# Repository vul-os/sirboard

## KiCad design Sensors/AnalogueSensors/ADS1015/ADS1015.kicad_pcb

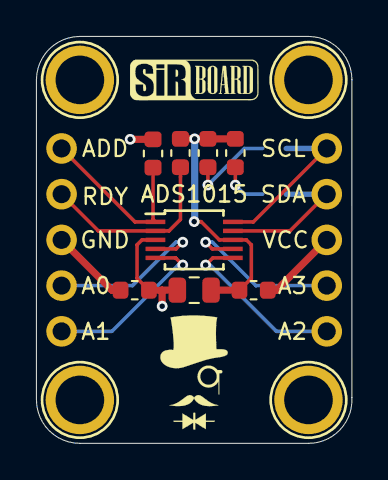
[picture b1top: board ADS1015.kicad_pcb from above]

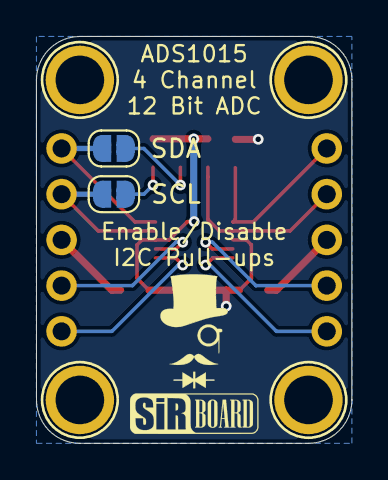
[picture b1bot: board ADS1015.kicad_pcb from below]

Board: 2 copper layers, 17.5 x 22.6 mm, 16 parts (4 on the bottom side), 14 nets.

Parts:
ADS1015: ADS1015IDGS; TSSOP-10_3x3mm_P0.5mm
C1: 1uF; C_0805_2012Metric
FB1, FB2: Ferrite_Bead; L_0603_1608Metric
H1, H2, H3, H4: MountingHole; MountingHole_M2.5_SirBoard
J1, J2: Conn_01x05; PinHeader_1x05_P2.54mm_Vertical
R1, R2, R3, R4: 10K; R_0603_1608Metric
SCL: SolderJumper_2_Open; SolderJumper-2_P1.3mm_Open_RoundedPad1.0x1.5mm
SDA: SolderJumper_2_Open; SolderJumper-2_P1.3mm_Open_RoundedPad1.0x1.5mm

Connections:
ADD: ADS1015.1, J1.1, R4.1
AIN0: ADS1015.4, J1.4
AIN1: ADS1015.5, J1.5
AIN2: ADS1015.6, J2.5
AIN3: ADS1015.7, J2.4
ALERT: ADS1015.2, J1.2, R3.1
GND: FB1.1, J1.3
GND_B: ADS1015.3, C1.2, FB1.2, R4.2
unnamed: R1.1, SCL.2
unnamed: R2.1, SDA.2
SCL: ADS1015.10, J2.1, SDA.1
SDA: ADS1015.9, J2.2, SCL.1
VCC: FB2.1, J2.3
VCC_B: ADS1015.8, C1.1, FB2.2, R1.2, R2.2, R3.2

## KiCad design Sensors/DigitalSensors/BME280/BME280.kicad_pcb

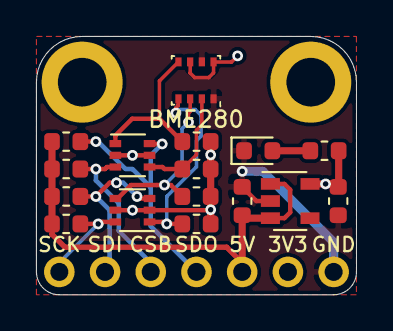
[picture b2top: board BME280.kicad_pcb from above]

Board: 2 copper layers, 17.8 x 14.4 mm, 19 parts (1 on the bottom side), 12 nets.

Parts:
BME280: BME280; Bosch_LGA-8_2.5x2.5mm_P0.65mm_ClockwisePinNumbering
C1, C2: 1uF; C_0603_1608Metric
D1: LED; LED_0603_1608Metric
H3, H4: MountingHole; MountingHole_2.7mm_M2.5_ISO14580_Pad
J1: Conn_01x07; PinHeader_1x07_P2.54mm_Vertical
Q1, Q2: BSS138DW; SOT-363_SC-70-6
R1, R2, R3, R4, R5, R7, R8, R9: 10K; R_0603_1608Metric
R6: 1K; R_0603_1608Metric
U1: AP2127K-3.3; SOT-23-5

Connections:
3V3: BME280.6, BME280.8, C2.1, J1.6, Q1.2, Q1.5, Q2.2, Q2.5, R1.2, R3.2, R5.2, R6.1, R8.2, U1.5
5V: C1.1, J1.5, R2.1, R4.1, R7.1, R9.1, U1.1, U1.3
CSB_3V3: BME280.2, Q2.4, R8.1
CSB_5V: J1.3, Q2.3, R9.2
GND: BME280.1, BME280.7, C1.2, C2.2, D1.1, J1.7, U1.2
unnamed: D1.2, R6.2
SCK_3V3: BME280.4, Q1.1, R1.1
SCK_5V: J1.1, Q1.6, R2.2
SDI_3V3: BME280.3, Q1.4, R3.1
SDI_5V: J1.2, Q1.3, R4.2
SDO_3V3: BME280.5, Q2.1, R5.1
SDO_5V: J1.4, Q2.6, R7.2

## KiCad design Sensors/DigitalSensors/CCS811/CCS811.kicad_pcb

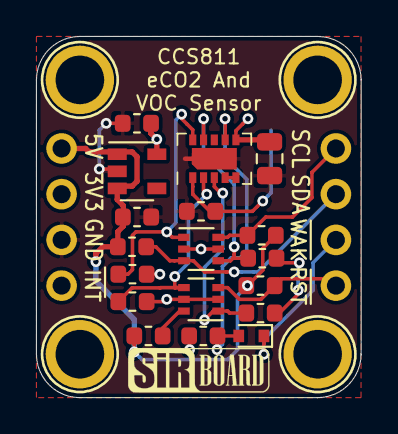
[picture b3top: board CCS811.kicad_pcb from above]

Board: 2 copper layers, 18.0 x 20.1 mm, 25 parts (1 on the bottom side), 15 nets.

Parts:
C1, C3: 1uF; C_0603_1608Metric
C5: 4.7uF; C_0805_2012Metric
D1: 1N4148; D_SOD-523
H1, H2, H3, H4: MountingHole; MountingHole_M2.5_SirBoard
J1, J2: Conn_01x04; PinHeader_1x04_P2.54mm_Vertical
JP1: SolderJumper_2_Open; SolderJumper-2_P1.3mm_Open_RoundedPad1.0x1.5mm
Q1, Q2: BSS138DW; SOT-363_SC-70-6
R1, R2, R3, R4, R5, R6, R7, R9: 4K7; R_0603_1608Metric
R8: 100K; R_0603_1608Metric
R11: 10K; R_0603_1608Metric
U1: AP2127K-3.3; SOT-23-5
U2: CCS811; AMS_LGA-10-1EP_2.7x4mm_P0.6mm

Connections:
3V3: C3.1, C5.1, J1.2, JP1.1, Q1.2, Q1.5, Q2.2, Q2.5, R1.2, R3.2, R5.2, R7.2, R8.1, U1.5, U2.6
5V: C1.1, J1.1, R2.1, R4.1, R6.1, R9.1, U1.1, U1.3
GND: C1.2, C3.2, C5.2, J1.3, R11.1, U1.2, U2.11
unnamed: JP1.2, R11.2, U2.1
unnamed: U2.4, U2.5
SCL_3V3: Q1.1, R1.1, U2.10
SCL_5V: J2.1, Q1.6, R2.2
SDA_3V3: Q1.4, R3.1, U2.9
SDA_5V: J2.2, Q1.3, R4.2
nINT3V3: Q2.1, R5.1, U2.3
nINT_5V: Q2.6, R6.2
nRST_3V3: Q2.4, R7.1, U2.2
nRST_5V: J2.4, Q2.3, R9.2
nWake_3V3: D1.2, R8.2, U2.7
nWake_5V: D1.1, J2.3

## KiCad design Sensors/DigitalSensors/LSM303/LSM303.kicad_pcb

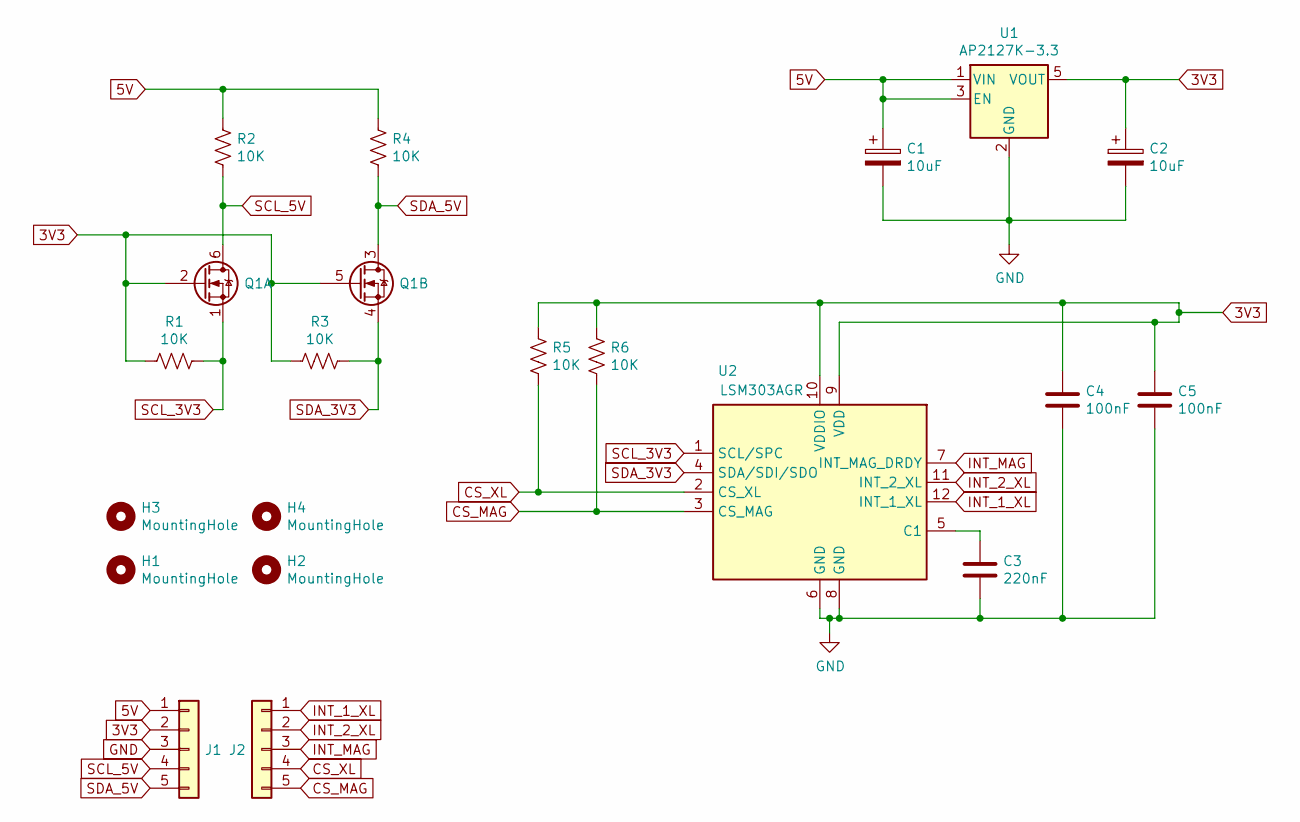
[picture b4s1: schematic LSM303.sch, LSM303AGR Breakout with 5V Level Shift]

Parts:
C1: 10uF; C_0805_2012Metric; Part C99366
C2: 10uF; C_0805_2012Metric; part C99366
C3: 220nF; C_0603_1608Metric; Part C106249
C4, C5: 100nF; C_0603_1608Metric; Part C42998
H1, H2, H3, H4: MountingHole; MountingHole_M2.5_SirBoard
J1, J2: Conn_01x05; PinHeader_1x05_P2.54mm_Vertical
Q1: BSS138DW; SOT-363_SC-70-6
R1, R2, R3, R4, R5, R6: 10K; R_0603_1608Metric; Part C99198
U1: AP2127K-3.3; SOT-23-5; Part C156285
U2: LSM303AGR; LGA-12_2x2mm_P0.5mm; Part C126671

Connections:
3V3: C2.1, C4.1, C5.1, J1.2, Q1.2 (G), Q1.5 (G), R1.2, R3.2, R5.1, R6.1, U1.5 (VOUT), U2.9 (VDD), U2.10 (VDDIO)
5V: C1.1, J1.1, R2.1, R4.1, U1.1 (VIN), U1.3 (EN)
CS_MAG: J2.5, R6.2, U2.3 (CS_MAG)
CS_XL: J2.4, R5.2, U2.2 (CS_XL)
GND: C1.2, C2.2, C3.2, C4.2, C5.2, J1.3, U1.2 (GND), U2.6 (GND), U2.8 (GND)
INT_1_XL: J2.1, U2.12 (INT_1_XL)
INT_2_XL: J2.2, U2.11 (INT_2_XL)
INT_MAG: J2.3, U2.7 (INT_MAG_DRDY)
unnamed: C3.1, U2.5 (C1)
SCL_3V3: Q1.1 (S), R1.1, U2.1 (SCL/SPC)
SCL_5V: J1.4, Q1.6 (D), R2.2
SDA_3V3: Q1.4 (S), R3.1, U2.4 (SDA/SDI/SDO)
SDA_5V: J1.5, Q1.3 (D), R4.2

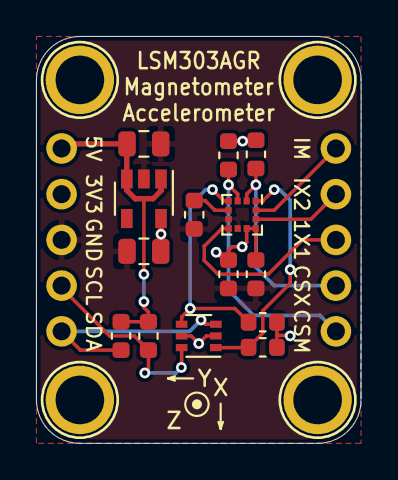
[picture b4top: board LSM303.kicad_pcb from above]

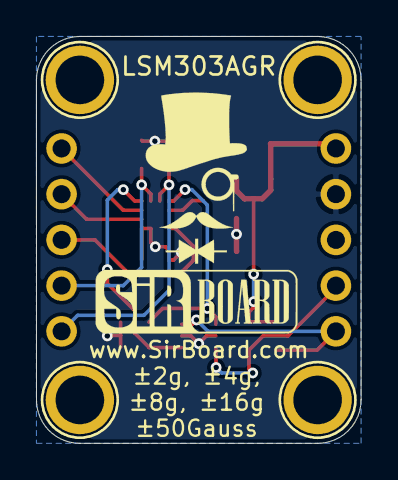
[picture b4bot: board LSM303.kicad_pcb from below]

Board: 2 copper layers, 18.0 x 22.6 mm, 20 parts (2 on the bottom side), 13 nets.

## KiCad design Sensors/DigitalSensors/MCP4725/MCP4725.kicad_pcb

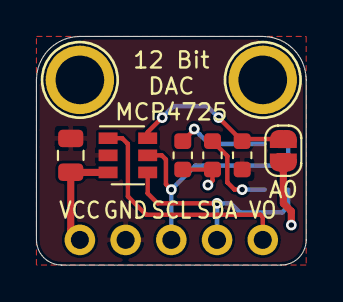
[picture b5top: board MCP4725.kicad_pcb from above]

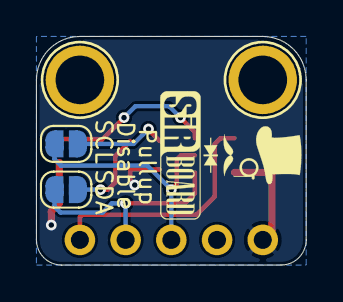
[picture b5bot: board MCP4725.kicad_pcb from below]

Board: 2 copper layers, 15.0 x 12.7 mm, 11 parts (2 on the bottom side), 8 nets.

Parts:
A0: SolderJumper_2_Open; SolderJumper-2_P1.3mm_Open_RoundedPad1.0x1.5mm
C1: 10uF; C_0805_2012Metric
H1, H2: MountingHole; MountingHole_M2.5_SirBoard
J1: Conn_01x05; PinHeader_1x05_P2.54mm_Vertical
MCP4725: MCP4725; SOT-23-6
R1, R2, R3: 10K; R_0603_1608Metric
SCL: SolderJumper_2_Open; SolderJumper-2_P1.3mm_Open_RoundedPad1.0x1.5mm
SDA: SolderJumper_2_Open; SolderJumper-2_P1.3mm_Open_RoundedPad1.0x1.5mm

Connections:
/A0: A0.2, MCP4725.6, R1.1
GND: C1.2, J1.2, MCP4725.2, R1.2
unnamed: R2.2, SCL.1
unnamed: R3.2, SDA.1
SCL: J1.3, MCP4725.5, SCL.2
SDA: J1.4, MCP4725.4, SDA.2
VCC: A0.1, C1.1, J1.1, MCP4725.3, R2.1, R3.1
VOUT: J1.5, MCP4725.1

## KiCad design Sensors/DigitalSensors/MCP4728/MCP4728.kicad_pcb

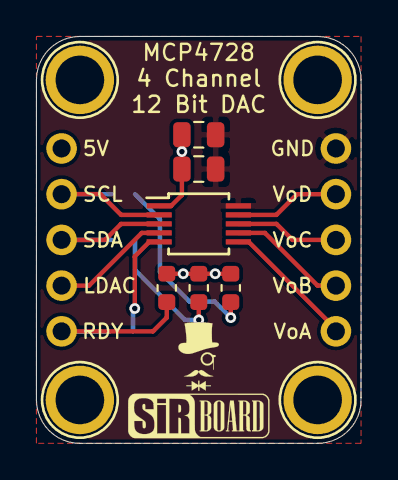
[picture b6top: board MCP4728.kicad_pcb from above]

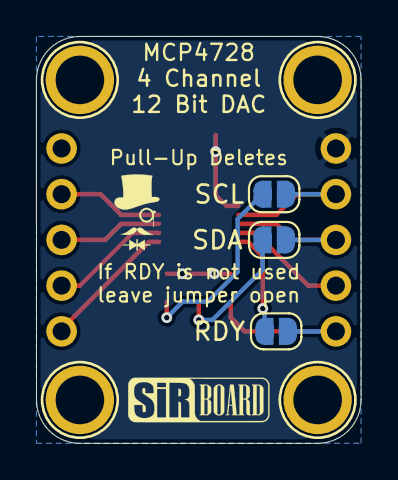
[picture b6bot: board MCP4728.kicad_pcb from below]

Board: 2 copper layers, 18.0 x 22.6 mm, 15 parts (5 on the bottom side), 13 nets.

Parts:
C1: 100nF; R_0805_2012Metric
C2: 10uF; R_0805_2012Metric
H1, H2, H3, H4: MountingHole; MountingHole_M2.5_SirBoard
J1, J2: Conn_01x05; PinHeader_1x05_P2.54mm_Vertical
R1: 100K; R_0603_1608Metric
R2, R3: 10K; R_0603_1608Metric
RDY: SolderJumper_2_Open; SolderJumper-2_P1.3mm_Open_RoundedPad1.0x1.5mm
SCL: SolderJumper_2_Open; SolderJumper-2_P1.3mm_Open_RoundedPad1.0x1.5mm
SDA: SolderJumper_2_Open; SolderJumper-2_P1.3mm_Open_RoundedPad1.0x1.5mm
U1: MCP4728; MSOP-10_3x3mm_P0.5mm

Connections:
GND: C1.2, C2.2, J2.1, U1.10
LDAC: J1.4, U1.4
unnamed: R2.2, SCL.1
unnamed: R3.2, SDA.1
unnamed: RDY.2, U1.5
RDY: J1.5, R1.2, RDY.1
SCL: J1.2, SCL.2, U1.2
SDA: J1.3, SDA.2, U1.3
VCC: C1.1, C2.1, J1.1, R1.1, R2.1, R3.1, U1.1
VoutA: J2.5, U1.6
VoutB: J2.4, U1.7
VoutC: J2.3, U1.8
VoutD: J2.2, U1.9
